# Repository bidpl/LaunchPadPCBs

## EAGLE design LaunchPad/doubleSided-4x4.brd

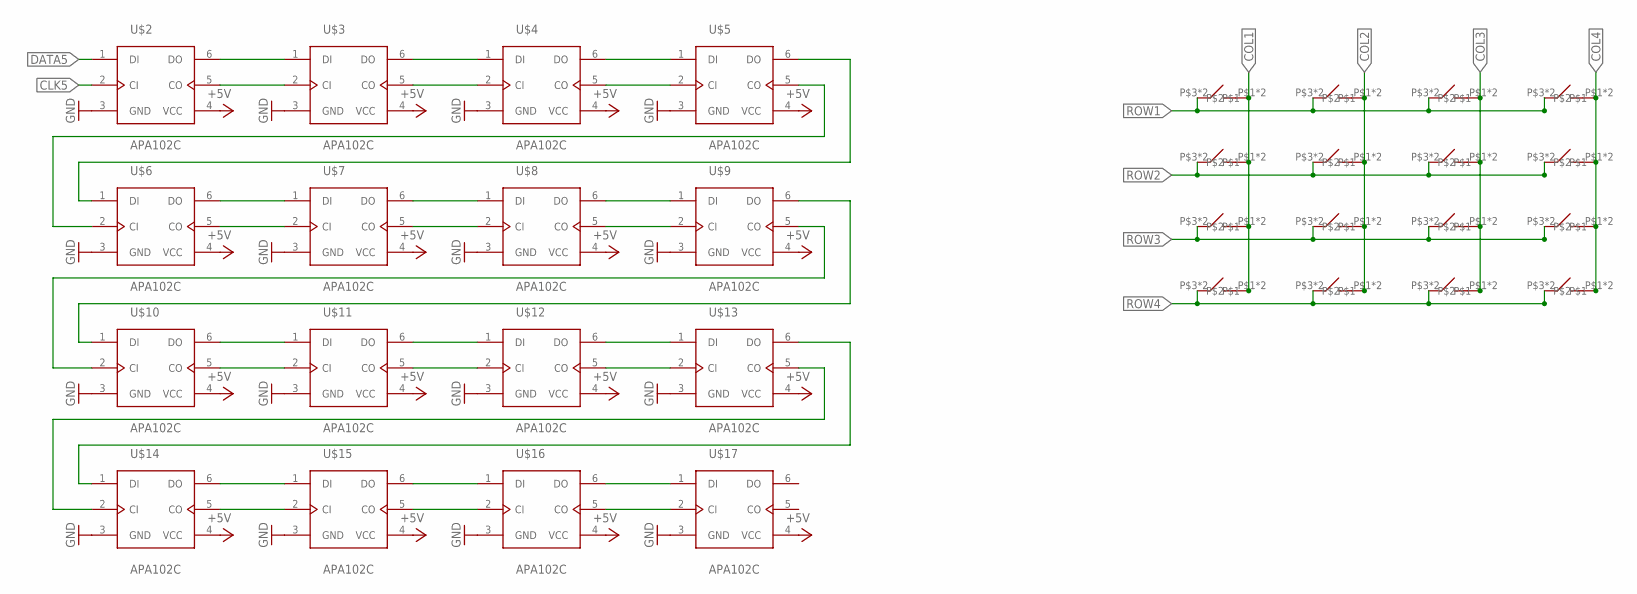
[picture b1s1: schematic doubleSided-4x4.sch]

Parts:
U$2, U$3, U$4, U$5, U$6, U$7, U$8, U$9, U$10, U$11, U$12, U$13, U$14, U$15, U$16, U$17: APA102C; APA102C-5050-SMD
U$18, U$19, U$20, U$21, U$22, U$23, U$24, U$25, U$26, U$27, U$28, U$29, U$30, U$31, U$32, U$33: SOFT-TACTILE-PUSHBUTTON; ADAFRUIT-SOFT-TACTILE-PUSHBUTTON

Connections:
5V: U$2.4 (VCC), U$3.4 (VCC), U$4.4 (VCC), U$5.4 (VCC), U$6.4 (VCC), U$7.4 (VCC), U$8.4 (VCC), U$9.4 (VCC), U$10.4 (VCC), U$11.4 (VCC), U$12.4 (VCC), U$13.4 (VCC), U$14.4 (VCC), U$15.4 (VCC), U$16.4 (VCC), U$17.4 (VCC)
CLK5: U$2.2 (CI)
COL1: U$18.P$1, U$18.P$2, U$22.P$1, U$22.P$2, U$26.P$1, U$26.P$2, U$30.P$1, U$30.P$2
COL2: U$19.P$1, U$19.P$2, U$23.P$1, U$23.P$2, U$27.P$1, U$27.P$2, U$31.P$1, U$31.P$2
COL3: U$20.P$1, U$20.P$2, U$24.P$1, U$24.P$2, U$28.P$1, U$28.P$2, U$32.P$1, U$32.P$2
COL4: U$21.P$1, U$21.P$2, U$25.P$1, U$25.P$2, U$29.P$1, U$29.P$2, U$33.P$1, U$33.P$2
DATA5: U$2.1 (DI)
GND: U$2.3 (GND), U$3.3 (GND), U$4.3 (GND), U$5.3 (GND), U$6.3 (GND), U$7.3 (GND), U$8.3 (GND), U$9.3 (GND), U$10.3 (GND), U$11.3 (GND), U$12.3 (GND), U$13.3 (GND), U$14.3 (GND), U$15.3 (GND), U$16.3 (GND), U$17.3 (GND)
unnamed: U$2.6 (DO), U$3.1 (DI)
unnamed: U$2.5 (CO), U$3.2 (CI)
unnamed: U$3.5 (CO), U$4.2 (CI)
unnamed: U$3.6 (DO), U$4.1 (DI)
unnamed: U$4.6 (DO), U$5.1 (DI)
unnamed: U$4.5 (CO), U$5.2 (CI)
unnamed: U$6.6 (DO), U$7.1 (DI)
unnamed: U$6.5 (CO), U$7.2 (CI)
unnamed: U$7.5 (CO), U$8.2 (CI)
unnamed: U$7.6 (DO), U$8.1 (DI)
unnamed: U$8.6 (DO), U$9.1 (DI)
unnamed: U$8.5 (CO), U$9.2 (CI)
unnamed: U$5.5 (CO), U$6.2 (CI)
unnamed: U$5.6 (DO), U$6.1 (DI)
unnamed: U$10.6 (DO), U$11.1 (DI)
unnamed: U$10.5 (CO), U$11.2 (CI)
unnamed: U$11.5 (CO), U$12.2 (CI)
unnamed: U$11.6 (DO), U$12.1 (DI)
unnamed: U$12.6 (DO), U$13.1 (DI)
unnamed: U$12.5 (CO), U$13.2 (CI)
unnamed: U$14.6 (DO), U$15.1 (DI)
unnamed: U$14.5 (CO), U$15.2 (CI)
unnamed: U$15.5 (CO), U$16.2 (CI)
unnamed: U$15.6 (DO), U$16.1 (DI)
unnamed: U$16.6 (DO), U$17.1 (DI)
unnamed: U$16.5 (CO), U$17.2 (CI)
unnamed: U$9.5 (CO), U$10.2 (CI)
unnamed: U$9.6 (DO), U$10.1 (DI)
unnamed: U$13.5 (CO), U$14.2 (CI)
unnamed: U$13.6 (DO), U$14.1 (DI)
ROW1: U$18.P$3, U$18.P$4, U$19.P$3, U$19.P$4, U$20.P$3, U$20.P$4, U$21.P$3, U$21.P$4
ROW2: U$22.P$3, U$22.P$4, U$23.P$3, U$23.P$4, U$24.P$3, U$24.P$4, U$25.P$3, U$25.P$4
ROW3: U$26.P$3, U$26.P$4, U$27.P$3, U$27.P$4, U$28.P$3, U$28.P$4, U$29.P$3, U$29.P$4
ROW4: U$30.P$3, U$30.P$4, U$31.P$3, U$31.P$4, U$32.P$3, U$32.P$4, U$33.P$3, U$33.P$4

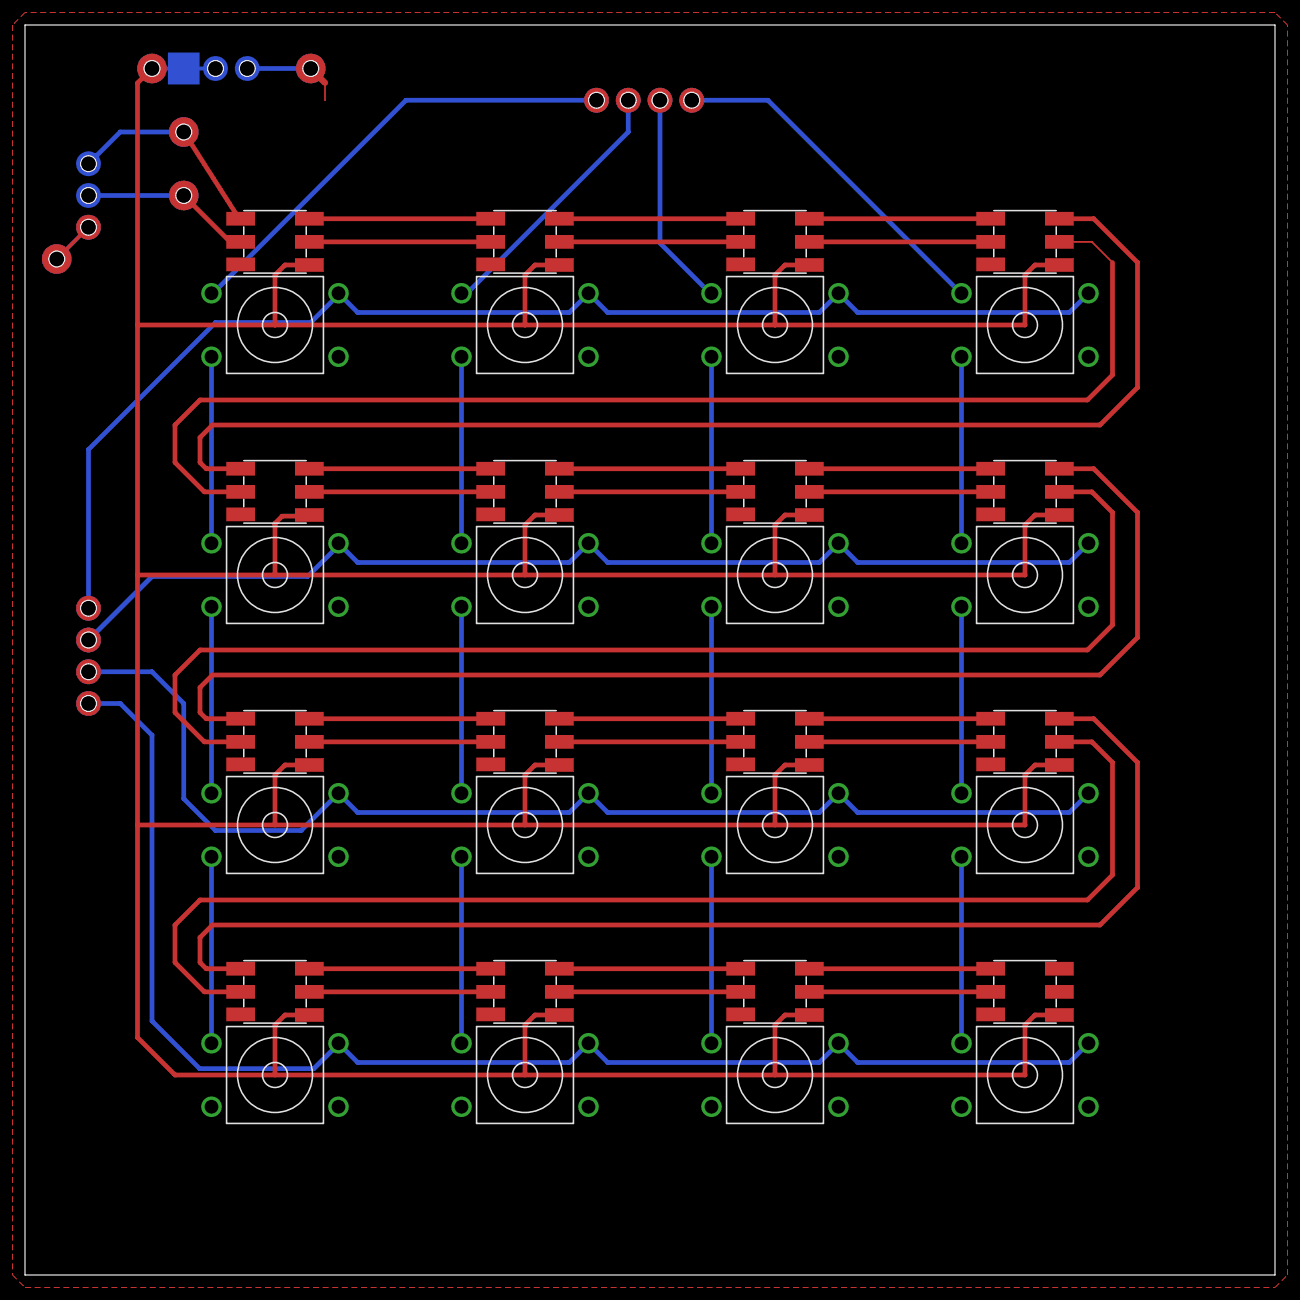
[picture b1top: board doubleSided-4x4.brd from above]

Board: 2 copper layers, 100.0 x 100.0 mm, 32 parts (0 on the bottom side), 40 nets.

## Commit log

2018-04-29 added APA201C 5050 LED Device
2018-04-29 Started final pcb
2018-04-29 Breakout board: added solderpads to holes
2018-05-06 Placed LEDS for 4x4 launchpad
2018-05-07 Restarted 4x4 board, still need vertical button jumpoers, button connection
2018-05-19 idk what I did
2018-05-19 Added jumpers for buttons vertically, added points for ends of button matrix. Added jumpers for led signals
2018-05-21 idk what I did again
2018-05-22 Added double sided board
2018-05-22 Added images of boards
2018-05-23 started illustrator transfer
2018-05-24 Worked on print versions
2018-05-25 Added ai, svg, and eps file versions for printing
2018-06-04 Made clearanes for othermill
2018-07-03 made 2 traces thicker
